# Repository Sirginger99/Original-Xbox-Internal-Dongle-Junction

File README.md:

Open source project creating a juntion to use for internalizing 
Xbox(OG) dongles. For those unfamiliar, this will allow you to 
internalize a dongle while retaining use of the controller port. 
It's a simple relay circuit that will switch to controller if 
one is plugged in, and default on the dongle if the controller 
is not in use. The goal was to make something simple, cheap, 
and small. There have been many variations of this that use 
switches, programmed chips, and spliced wires. This design 
removes the need for any of those. Please note that these are 
designed for one internal dongle per port. Stacking multiple 
dongles onto the same port may require a switch or additional 
materials. The materials document lists everything used on the 
PCB, along with it's matching connectors.

The pin positions are identical on the "Mobo" and "Controllers" 
connectors. This requires a cross cable be used from the "Mobo" 
connector to the motherboard. The controllers plug dirctly to the 
junction.

The "Shield" connector is for grounding the shields of 
the controller ports. The ports themselves will need to be 
insulated from the Xbox's metal cage. It is also necessary to 
verify that the connector on the controller itself has been 
grounded. While some aftermarket controllers may already be 
grounded, others will require some solder on the black wire to the
metal shield.

The "Xerc" connector are for those who have a Xerc 2 mod and wish
to internalize a dvd dongle. The wire that would normally bridge 
the two can just be plugged into the marked pin. This is connected
to both dongle positions.

For those unable to view the materials file, a picture is attached below.

Revision 1. 
Dimensions: 55 x 33.5 x 13.4mm. 
The difference between this and beta is a designated spot for the 
diodes. Originally, they would have been soldered across the points. 
This design was changed for complete assembly upon ordering, and an 
attempt to ease the mounting process by including all parts on the 
same side of the pcb.

Revision 2. 
Dimensions: 40 x 35.5 x 13.4mm. 
All the same features as revision 1, just slightly smaller.

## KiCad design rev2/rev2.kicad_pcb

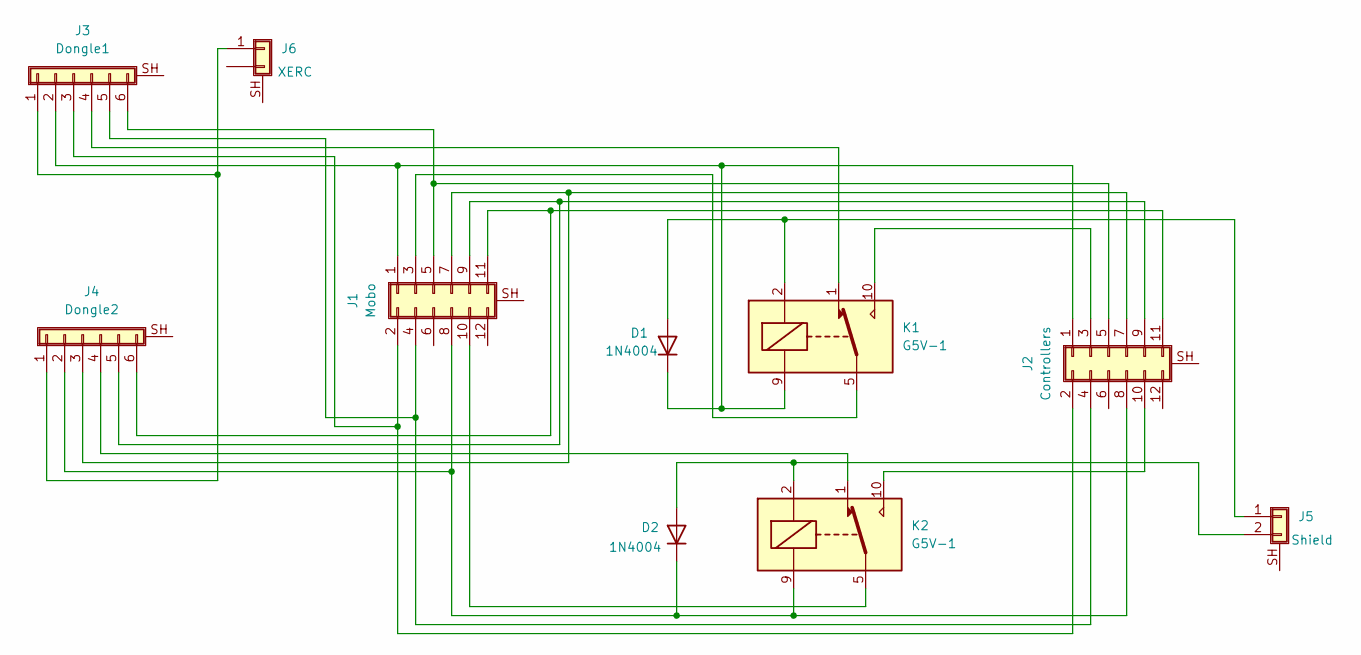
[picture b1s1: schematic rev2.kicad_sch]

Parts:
D1, D2: 1N4004; D_DO-41_SOD81_P10.16mm_Horizontal
J1: Mobo; JST_PHD_S12B-PHDSS_2x06_P2.00mm_Horizontal
J2: Controllers; JST_PHD_S12B-PHDSS_2x06_P2.00mm_Horizontal
J3: Dongle1; Molex_PicoBlade_53261-0671_1x06-1MP_P1.25mm_Horizontal
J4: Dongle2; Molex_PicoBlade_53261-0671_1x06-1MP_P1.25mm_Horizontal
J5: Shield; Molex_PicoBlade_53261-0271_1x02-1MP_P1.25mm_Horizontal
J6: Xerc; Molex_PicoBlade_53261-0271_1x02-1MP_P1.25mm_Horizontal
K1, K2: G5V-1; Relay_SPDT_Omron_G5V-1

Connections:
unnamed: D1.2 (A), J5.1, K1.2
unnamed: D1.1 (K), J1.1, J2.1, J3.2, K1.9
unnamed: D2.2 (A), J5.2, K2.2
unnamed: D2.1 (K), J1.8, J2.8, J4.2, K2.9
unnamed: J1.2, J2.2, J3.3
unnamed: J1.3, K1.5, K1.6
unnamed: J1.4, J2.4, J3.5
unnamed: J1.5, J2.5, J3.6
unnamed: J1.7, J2.7, J4.3
unnamed: J1.9, J2.9, J4.5
unnamed: J1.10, K2.5, K2.6
unnamed: J1.11, J2.11, J4.6
unnamed: J2.3, K1.10
unnamed: J2.10, K2.10
unnamed: J3.1, J4.1, J6.1
unnamed: J3.4, K1.1
unnamed: J4.4, K2.1

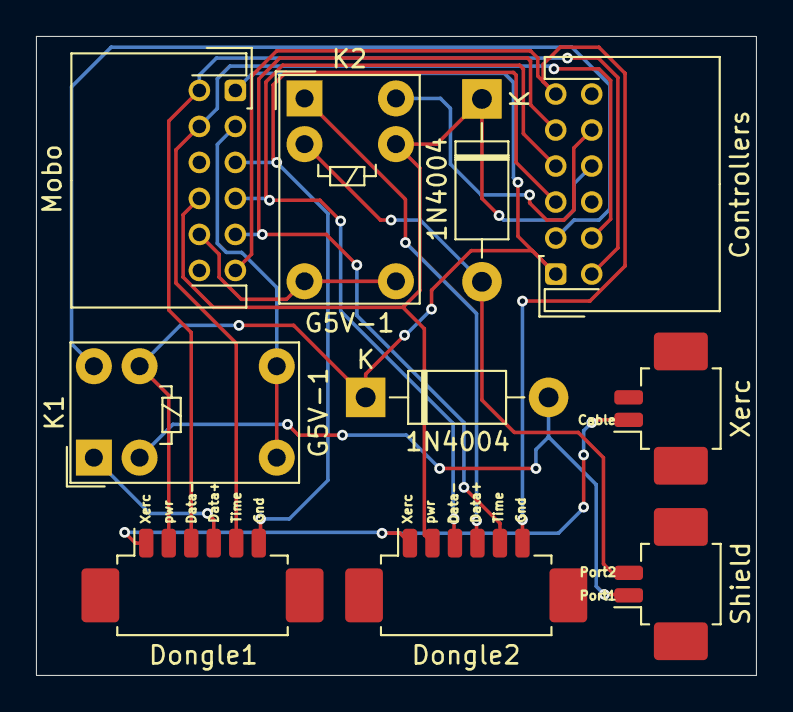
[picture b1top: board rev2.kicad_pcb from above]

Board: 2 copper layers, 40.0 x 35.5 mm, 10 parts (0 on the bottom side), 17 nets.

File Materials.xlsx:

Comments | Position | Manufature# | JLCPCB# | Digikey# | Connector
Mobo,Controllers | J1, J2 | S12B-PHDSS(LF)(SN) | C161673 | 455-S12B-PHDSS-ND | PHDR-12VS
Dongles | J3, J4 | 532610671 | C99277 | WM7624CT-ND | 510210600
Xerc,Shield | J5, J6 | 532610271 | C177225 | WM7620CT-ND | 510210200
Relay | K1, K2 | G5V-1 DC5 | C28695 | 39-G5V-1DC5-ND
Diode | D1, D2 | 1N4004 | C3058 | 1N4004DICT-ND

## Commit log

2025-03-08 Reorganize root folder
